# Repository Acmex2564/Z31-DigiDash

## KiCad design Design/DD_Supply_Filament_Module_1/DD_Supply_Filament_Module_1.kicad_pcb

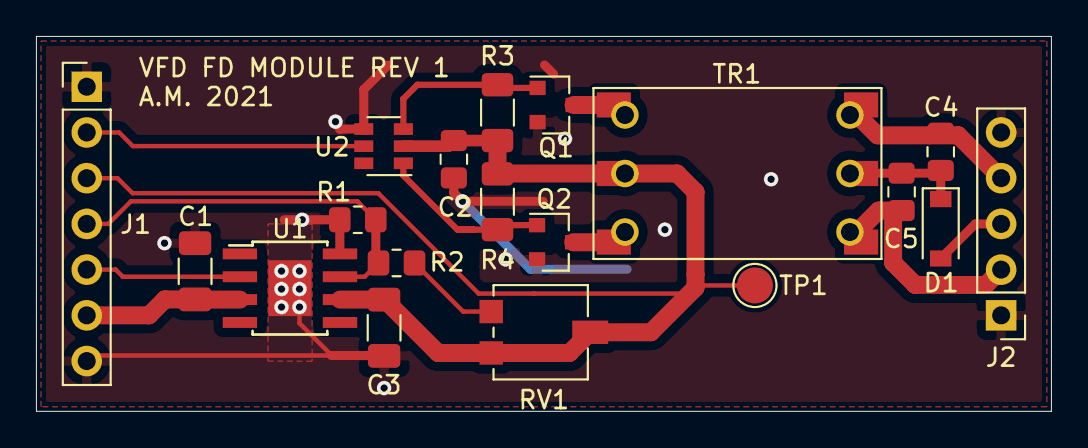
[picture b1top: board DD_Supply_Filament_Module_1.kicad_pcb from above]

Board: 2 copper layers, 56.4 x 20.8 mm, 19 parts (0 on the bottom side), 15 nets.

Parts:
C1, C3: 10uF X7R; C_1206_3216Metric_Pad1.33x1.80mm_HandSolder
C2, C4, C5: 100nF X7R; C_0805_2012Metric_Pad1.18x1.45mm_HandSolder
D1: D_Zener; D_SOD-123
J1: Conn_01x07_Male; PinHeader_1x07_P2.54mm_Vertical
J2: Conn_01x05_Male; PinHeader_1x05_P2.54mm_Vertical
Q1, Q2: SSM3K329R; SOT-23
R1: 30k; R_0805_2012Metric_Pad1.20x1.40mm_HandSolder
R2: 180k; R_0805_2012Metric_Pad1.20x1.40mm_HandSolder
R3, R4: 4.7k; R_1206_3216Metric_Pad1.30x1.75mm_HandSolder
RV1: 100k; Potentiometer_Vishay_TS53YL_Vertical
TP1: TestPoint; TestPoint_Pad_D2.0mm
TR1: Wuerth_750316031; HV_Supply_Transformer_FerroXCube-Wuerth
U1: TPS7A7001DDA; TI_SO-PowerPAD-8
U2: SN6505ADBV; SOT-23-6

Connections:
Filament_Bias: D1.2, J2.3
Filament_Out_A: C4.2, J2.4, TR1.6
Filament_Out_B: C5.2, J2.2, TR1.4
GND: C1.1, C2.2, C3.2, J1.1, J1.7, J2.1, J2.5, Q1.2, Q2.2, R1.2, U1.8, U1.9, U2.4
Invert_Enable: J1.2, U2.5
unnamed: C4.1, C5.1, D1.1, TR1.5
unnamed: Q1.1, R3.2, U2.3
unnamed: Q1.3, TR1.1
unnamed: Q2.1, R4.1, U2.1
unnamed: Q2.3, TR1.3
unnamed: R2.1, RV1.3
Reg_Adj: J1.4, R1.1, R2.2, U1.7
Reg_Enable: J1.5, U1.2
V_Filament_DC: C2.1, C3.1, J1.3, R3.1, R4.2, RV1.1, RV1.2, TP1.1, TR1.2, U1.6, U2.2
V_IN: C1.2, J1.6, U1.3
